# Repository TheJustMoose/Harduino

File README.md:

# Harduino

HardDuino is a 'Hard Arduino'
This is the clone of Arduino.
Project goals:
* ease of fastening
* compatible shields
* small sizes

How to use?

Copy content of template dir into C:\Program Files\KiCad\share\kicad\template\HardDuino

Add lib folder into KiCad libraries

Create 'new project from template' Harduino

Create your shield!
(Or use existing shield)

Enjoy!

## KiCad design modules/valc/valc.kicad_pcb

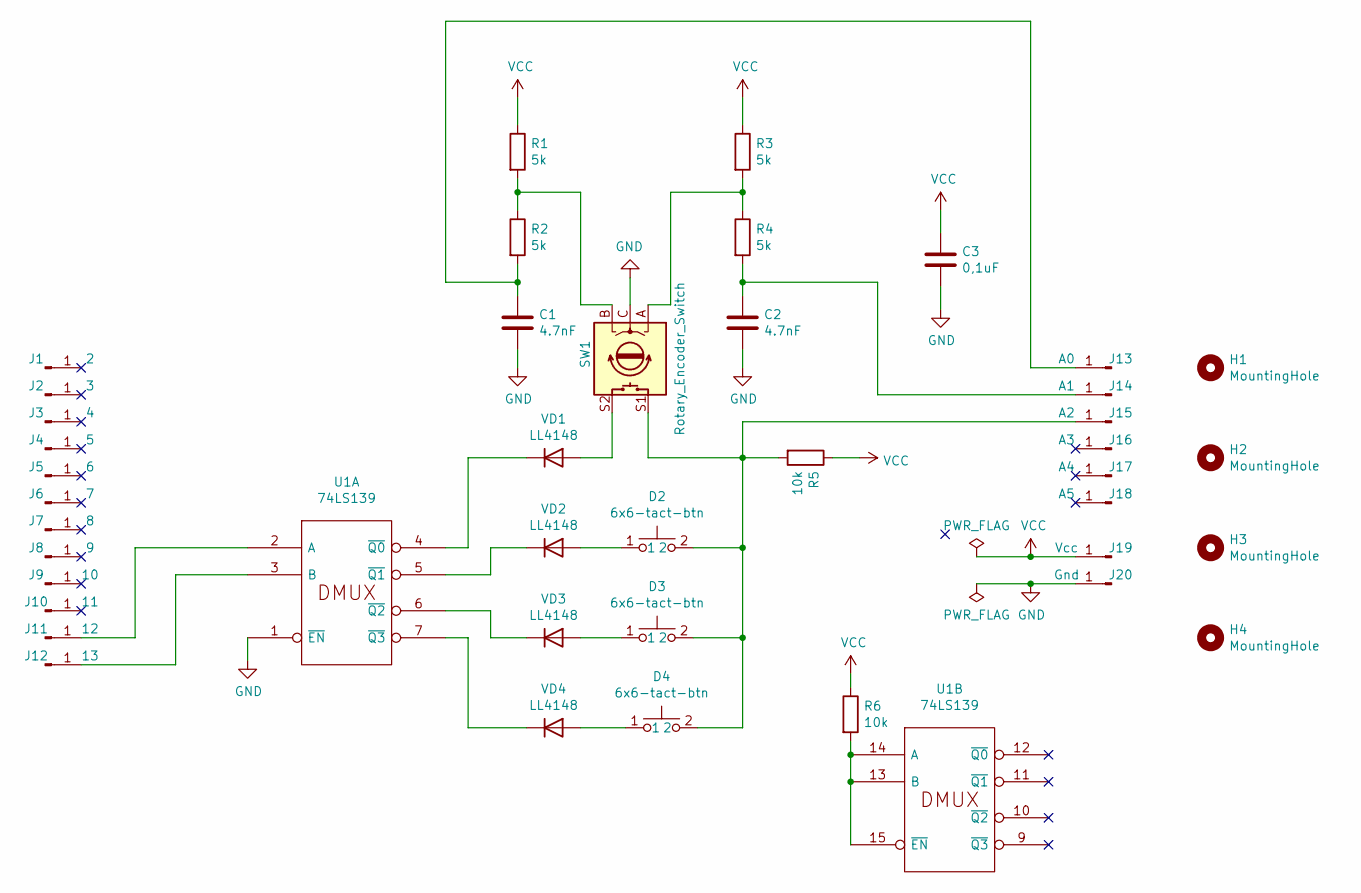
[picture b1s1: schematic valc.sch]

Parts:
C1, C2: 4.7nF; C_0805_2012Metric_Pad1.15x1.40mm_HandSolder
C3: 0,1uF; C_0805_2012Metric_Pad1.15x1.40mm_HandSolder
D2, D3, D4: 6x6-tact-btn
H1, H2, H3, H4: MountingHole; MountingHole_3.2mm_M3
J1: 2; PinHeader_1x01_P2.54mm_Vertical
J2: 3; PinHeader_1x01_P2.54mm_Vertical
J3: 4; PinHeader_1x01_P2.54mm_Vertical
J4: 5; PinHeader_1x01_P2.54mm_Vertical
J5: 6; PinHeader_1x01_P2.54mm_Vertical
J6: 7; PinHeader_1x01_P2.54mm_Vertical
J7: 8; PinHeader_1x01_P2.54mm_Vertical
J8: 9; PinHeader_1x01_P2.54mm_Vertical
J9: 10; PinHeader_1x01_P2.54mm_Vertical
J10: 11; PinHeader_1x01_P2.54mm_Vertical
J11: 12; PinHeader_1x01_P2.54mm_Vertical
J12: 13; PinHeader_1x01_P2.54mm_Vertical
J13: A0; PinHeader_1x01_P2.54mm_Vertical
J14: A1; PinHeader_1x01_P2.54mm_Vertical
J15: A2; PinHeader_1x01_P2.54mm_Vertical
J16: A3; PinHeader_1x01_P2.54mm_Vertical
J17: A4; PinHeader_1x01_P2.54mm_Vertical
J18: A5; PinHeader_1x01_P2.54mm_Vertical
J19: Vcc; PinHeader_1x01_P2.54mm_Vertical
J20: Gnd; PinHeader_1x01_P2.54mm_Vertical
R1, R2, R3, R4: 5k; R_0805_2012Metric_Pad1.15x1.40mm_HandSolder
R5, R6: 10k; R_0805_2012Metric_Pad1.15x1.40mm_HandSolder
SW1: Rotary_Encoder_Switch; RotaryEncoder_Alps_EC11E-Switch_Vertical_H20mm
U1: 74LS139; SOIC-16_3.9x9.9mm_P1.27mm
VD1, VD2, VD3, VD4: LL4148; D_MiniMELF

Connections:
GND: C1.2, C2.2, C3.2, J20.1, SW1.C, U1.1 (~EN), U1.8 (GND)
unnamed: C1.1, J13.1, R2.2
unnamed: C2.1, J14.1, R4.2
unnamed: D2.1, VD2.2 (A)
unnamed: D2.2, D3.2, D4.2, J15.1, R5.2, SW1.S1
unnamed: D3.1, VD3.2 (A)
unnamed: D4.1, VD4.2 (A)
unnamed: J11.1, U1.2 (A)
unnamed: J12.1, U1.3 (B)
unnamed: R1.2, R2.1, SW1.B
unnamed: R3.2, R4.1, SW1.A
unnamed: R6.2, U1.13 (B), U1.14 (A), U1.15 (~EN)
unnamed: SW1.S2, VD1.2 (A)
unnamed: U1.4 (~Q0), VD1.1 (K)
unnamed: U1.5 (~Q1), VD2.1 (K)
unnamed: U1.6 (~Q2), VD3.1 (K)
unnamed: U1.7 (~Q3), VD4.1 (K)
VCC: C3.1, J19.1, R1.1, R3.1, R5.1, R6.1, U1.16 (VCC)

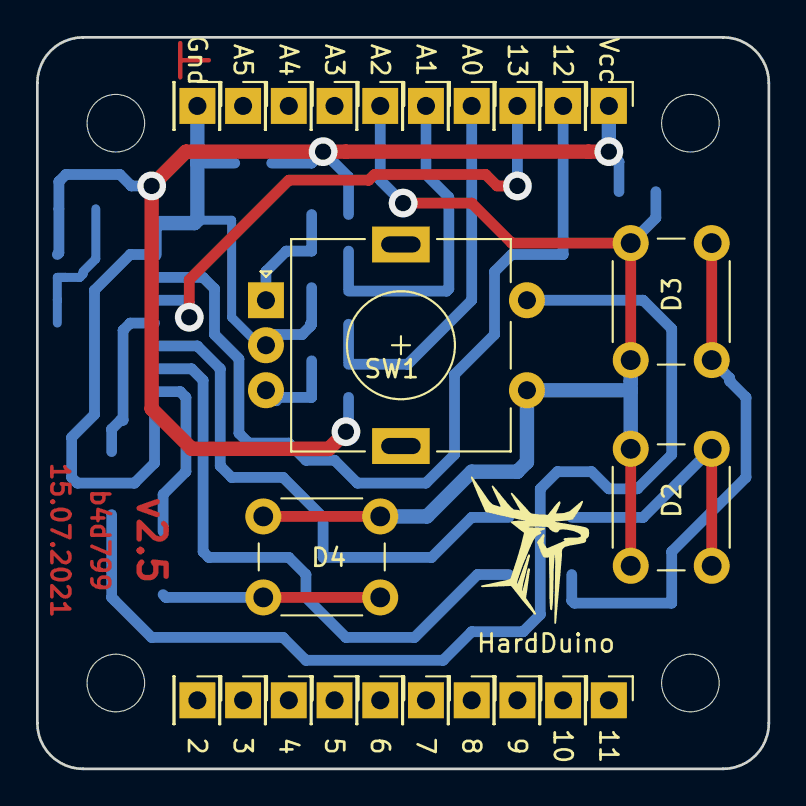
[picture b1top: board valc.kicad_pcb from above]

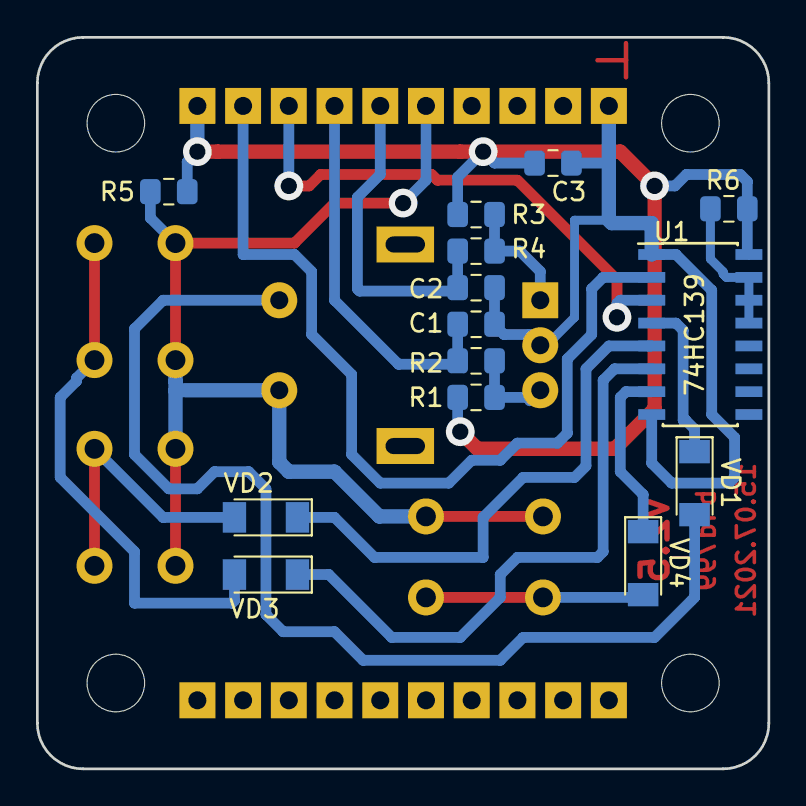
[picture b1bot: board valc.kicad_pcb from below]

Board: 2 copper layers, 40.6 x 40.6 mm, 42 parts (14 on the bottom side), 18 nets.

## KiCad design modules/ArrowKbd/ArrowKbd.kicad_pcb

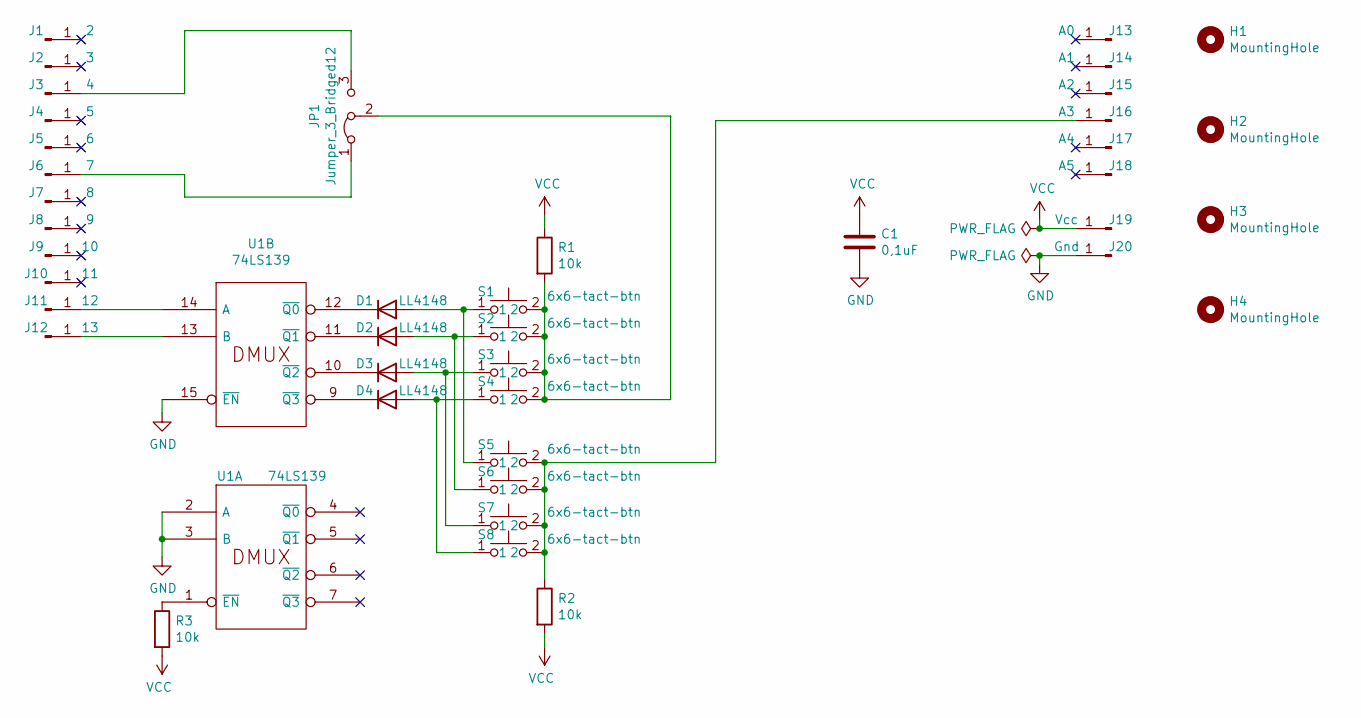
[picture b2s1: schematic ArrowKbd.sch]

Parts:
C1: 0,1uF; C_0805_2012Metric_Pad1.15x1.40mm_HandSolder
D1, D2, D3, D4: LL4148; D_MiniMELF
H1, H2, H3, H4: MountingHole; MountingHole_3.2mm_M3
J1: 2; PinHeader_1x01_P2.54mm_Vertical
J2: 3; PinHeader_1x01_P2.54mm_Vertical
J3: 4; PinHeader_1x01_P2.54mm_Vertical
J4: 5; PinHeader_1x01_P2.54mm_Vertical
J5: 6; PinHeader_1x01_P2.54mm_Vertical
J6: 7; PinHeader_1x01_P2.54mm_Vertical
J7: 8; PinHeader_1x01_P2.54mm_Vertical
J8: 9; PinHeader_1x01_P2.54mm_Vertical
J9: 10; PinHeader_1x01_P2.54mm_Vertical
J10: 11; PinHeader_1x01_P2.54mm_Vertical
J11: 12; PinHeader_1x01_P2.54mm_Vertical
J12: 13; PinHeader_1x01_P2.54mm_Vertical
J13: A0; PinHeader_1x01_P2.54mm_Vertical
J14: A1; PinHeader_1x01_P2.54mm_Vertical
J15: A2; PinHeader_1x01_P2.54mm_Vertical
J16: A3; PinHeader_1x01_P2.54mm_Vertical
J17: A4; PinHeader_1x01_P2.54mm_Vertical
J18: A5; PinHeader_1x01_P2.54mm_Vertical
J19: Vcc; PinHeader_1x01_P2.54mm_Vertical
J20: Gnd; PinHeader_1x01_P2.54mm_Vertical
JP1: Jumper_3_Bridged12; PinHeader_1x03_P2.54mm_Vertical
R1, R2, R3: 10k; R_0805_2012Metric_Pad1.15x1.40mm_HandSolder
S1, S2, S3, S4, S5, S6, S7, S8: 6x6-tact-btn
U1: 74LS139; SOIC-16_3.9x9.9mm_P1.27mm

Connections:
GND: C1.2, J20.1, U1.2 (A), U1.3 (B), U1.8 (GND), U1.15 (~EN)
unnamed: D1.1 (K), U1.12 (~Q0)
unnamed: D1.2 (A), S1.1, S5.1
unnamed: D2.1 (K), U1.11 (~Q1)
unnamed: D2.2 (A), S2.1, S6.1
unnamed: D3.1 (K), U1.10 (~Q2)
unnamed: D3.2 (A), S3.1, S7.1
unnamed: D4.1 (K), U1.9 (~Q3)
unnamed: D4.2 (A), S4.1, S8.1
unnamed: J3.1, JP1.3 (B)
unnamed: J6.1, JP1.1 (A)
unnamed: J11.1, U1.14 (A)
unnamed: J12.1, U1.13 (B)
unnamed: J16.1, R2.1, S5.2, S6.2, S7.2, S8.2
unnamed: JP1.2 (C), R1.2, S1.2, S2.2, S3.2, S4.2
unnamed: R3.1, U1.1 (~EN)
VCC: C1.1, J19.1, R1.1, R2.2, R3.2, U1.16 (VCC)

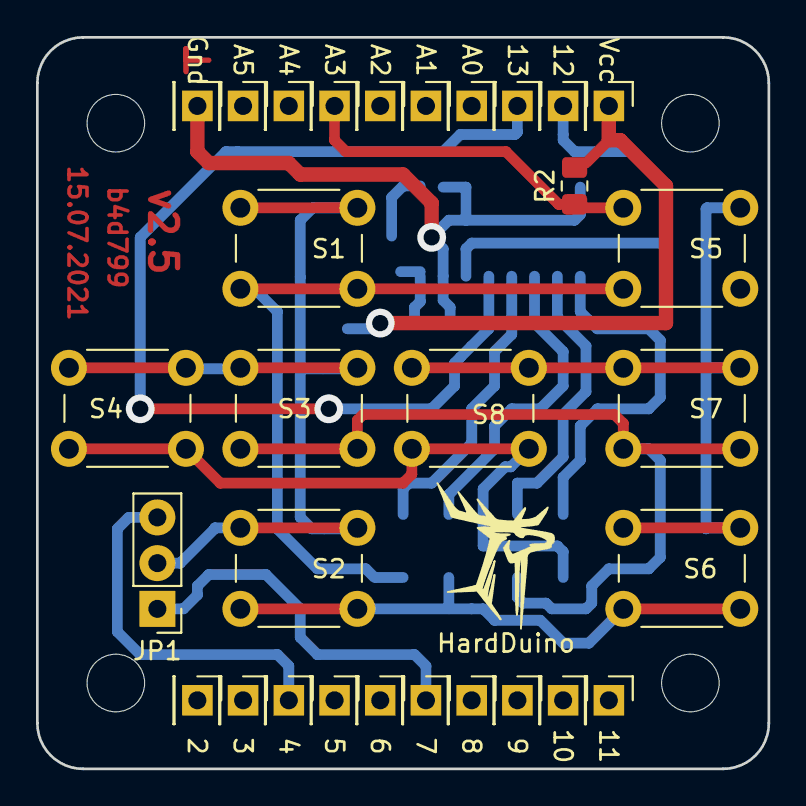
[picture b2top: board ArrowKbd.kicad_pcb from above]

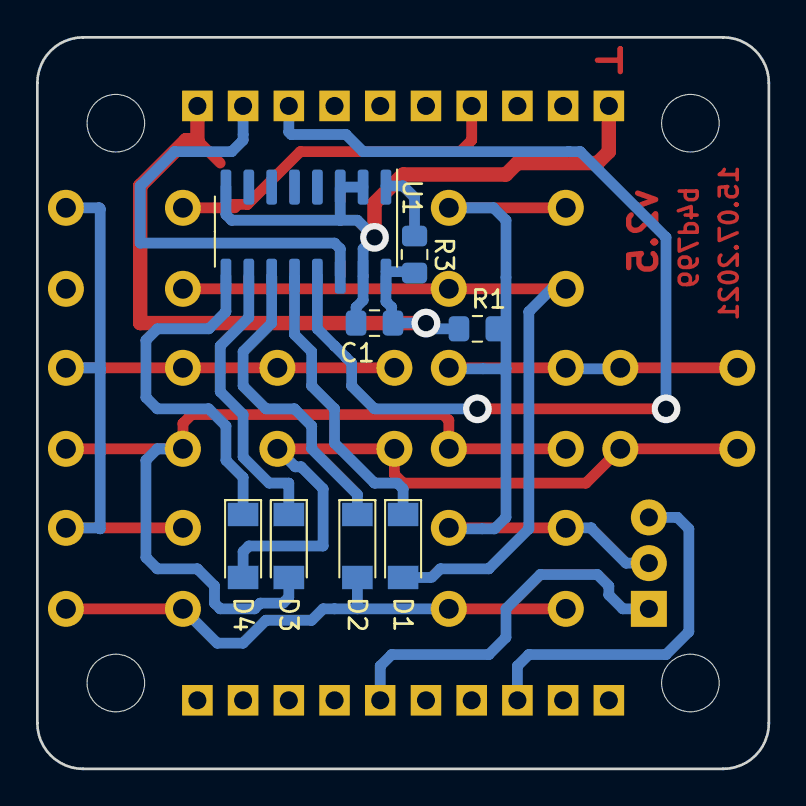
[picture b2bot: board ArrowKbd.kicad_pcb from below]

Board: 2 copper layers, 40.6 x 40.6 mm, 42 parts (8 on the bottom side), 17 nets.

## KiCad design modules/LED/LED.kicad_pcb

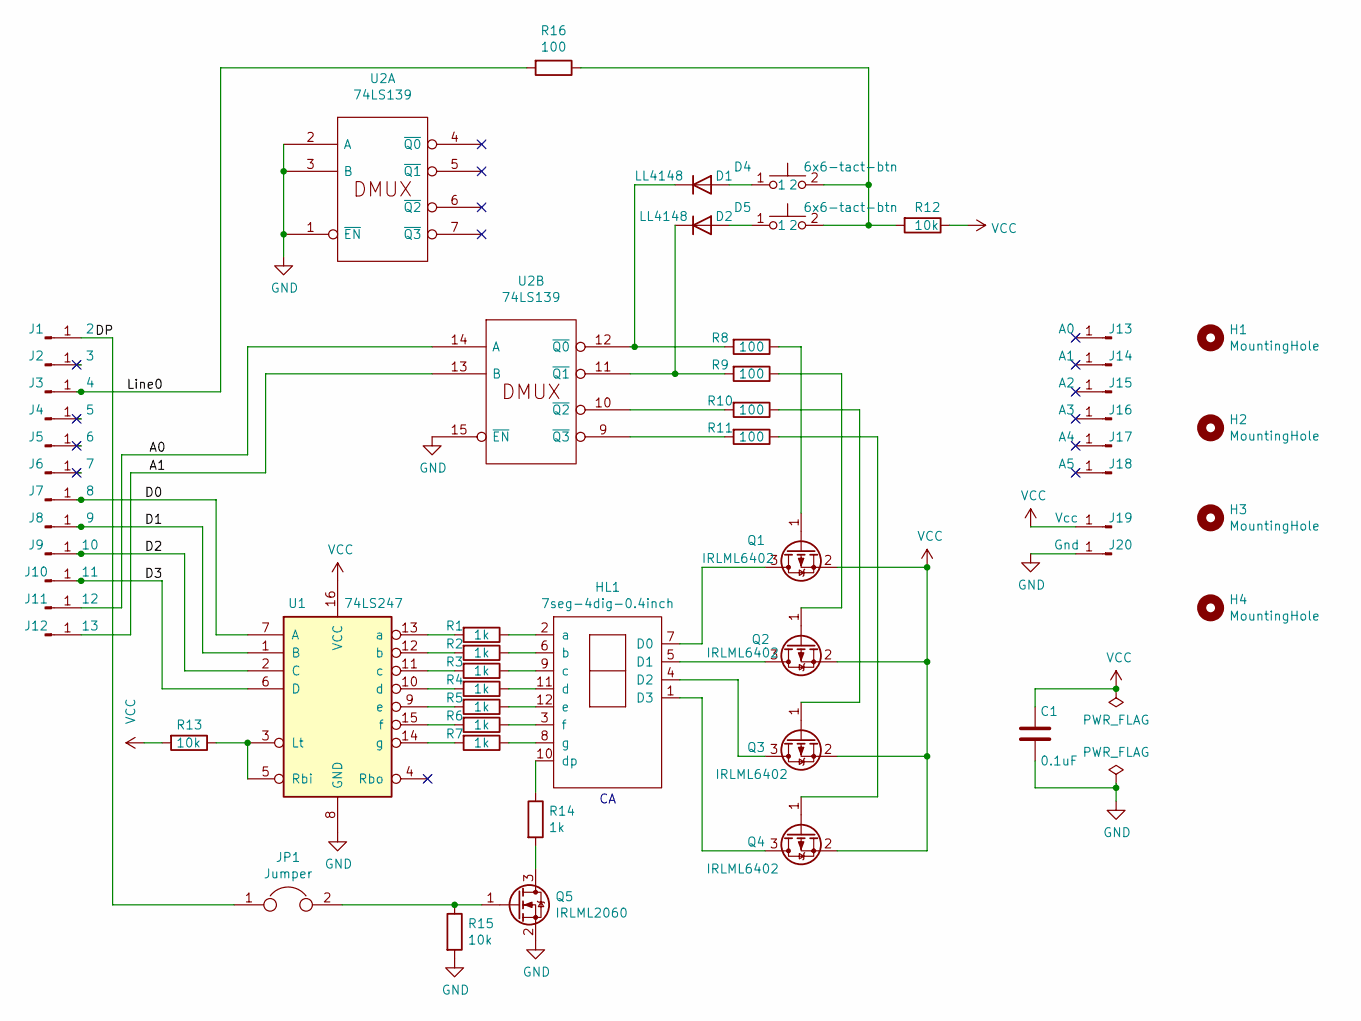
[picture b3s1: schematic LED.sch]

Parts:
C1: 0.1uF; C_0805_2012Metric_Pad1.15x1.40mm_HandSolder
D1, D2: LL4148; D_MiniMELF
D4, D5: 6x6-tact-btn
H1, H2, H3, H4: MountingHole; MountingHole_3.2mm_M3
HL1: 7seg-4dig-0.4inch
J1: 2; PinHeader_1x01_P2.54mm_Vertical
J2: 3; PinHeader_1x01_P2.54mm_Vertical
J3: 4; PinHeader_1x01_P2.54mm_Vertical
J4: 5; PinHeader_1x01_P2.54mm_Vertical
J5: 6; PinHeader_1x01_P2.54mm_Vertical
J6: 7; PinHeader_1x01_P2.54mm_Vertical
J7: 8; PinHeader_1x01_P2.54mm_Vertical
J8: 9; PinHeader_1x01_P2.54mm_Vertical
J9: 10; PinHeader_1x01_P2.54mm_Vertical
J10: 11; PinHeader_1x01_P2.54mm_Vertical
J11: 12; PinHeader_1x01_P2.54mm_Vertical
J12: 13; PinHeader_1x01_P2.54mm_Vertical
J13: A0; PinHeader_1x01_P2.54mm_Vertical
J14: A1; PinHeader_1x01_P2.54mm_Vertical
J15: A2; PinHeader_1x01_P2.54mm_Vertical
J16: A3; PinHeader_1x01_P2.54mm_Vertical
J17: A4; PinHeader_1x01_P2.54mm_Vertical
J18: A5; PinHeader_1x01_P2.54mm_Vertical
J19: Vcc; PinHeader_1x01_P2.54mm_Vertical
J20: Gnd; PinHeader_1x01_P2.54mm_Vertical
JP1: Jumper; PinHeader_1x02_P2.54mm_Vertical
Q1, Q2, Q3, Q4: IRLML6402; SOT-23
Q5: IRLML2060; SOT-23
R1, R2, R3, R4, R5, R6, R7, R14: 1k; R_0805_2012Metric_Pad1.15x1.40mm_HandSolder
R8, R9, R10, R11, R16: 100; R_0805_2012Metric_Pad1.15x1.40mm_HandSolder
R12, R13, R15: 10k; R_0805_2012Metric_Pad1.15x1.40mm_HandSolder
U1: 74LS247; SOIC-16_3.9x9.9mm_P1.27mm
U2: 74LS139; SOIC-16_3.9x9.9mm_P1.27mm

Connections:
/A0: J11.1, U2.14 (A)
/A1: J12.1, U2.13 (B)
/D0: J7.1, U1.7 (A)
/D1: J8.1, U1.1 (B)
/D2: J9.1, U1.2 (C)
/D3: J10.1, U1.6 (D)
/DP: J1.1, JP1.1
/Line0: J3.1, R16.2
GND: C1.2, J20.1, Q5.2 (S), R15.2, U1.8 (GND), U2.1 (~EN), U2.2 (A), U2.3 (B), U2.8 (GND), U2.15 (~EN)
unnamed: D1.1 (K), R8.2, U2.12 (~Q0)
unnamed: D1.2 (A), D4.1
unnamed: D2.1 (K), R9.2, U2.11 (~Q1)
unnamed: D2.2 (A), D5.1
unnamed: D4.2, D5.2, R12.2, R16.1
unnamed: HL1.1 (D3), Q4.3 (D)
unnamed: HL1.2 (a), R1.1
unnamed: HL1.3 (f), R6.1
unnamed: HL1.4 (D2), Q3.3 (D)
unnamed: HL1.5 (D1), Q2.3 (D)
unnamed: HL1.6 (b), R2.1
unnamed: HL1.7 (D0), Q1.3 (D)
unnamed: HL1.8 (g), R7.1
unnamed: HL1.9 (c), R3.1
unnamed: HL1.10 (dp), R14.1
unnamed: HL1.11 (d), R4.1
unnamed: HL1.12 (e), R5.1
unnamed: JP1.2, Q5.1 (G), R15.1
unnamed: Q1.1 (G), R8.1
unnamed: Q2.1 (G), R9.1
unnamed: Q3.1 (G), R10.1
unnamed: Q4.1 (G), R11.1
unnamed: Q5.3 (D), R14.2
unnamed: R1.2, U1.13 (a)
unnamed: R2.2, U1.12 (b)
unnamed: R3.2, U1.11 (c)
unnamed: R4.2, U1.10 (d)
unnamed: R5.2, U1.9 (e)
unnamed: R6.2, U1.15 (f)
unnamed: R7.2, U1.14 (g)
unnamed: R10.2, U2.10 (~Q2)
unnamed: R11.2, U2.9 (~Q3)
unnamed: R13.1, U1.3 (Lt), U1.5 (Rbi)
VCC: C1.1, J19.1, Q1.2 (S), Q2.2 (S), Q3.2 (S), Q4.2 (S), R12.1, R13.2, U1.16 (VCC), U2.16 (VCC)

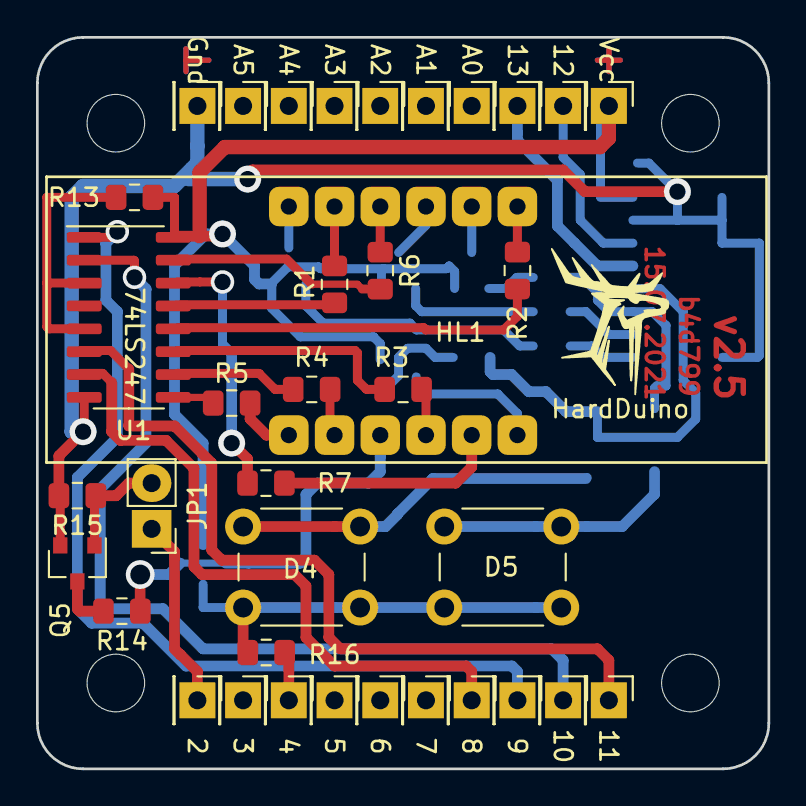
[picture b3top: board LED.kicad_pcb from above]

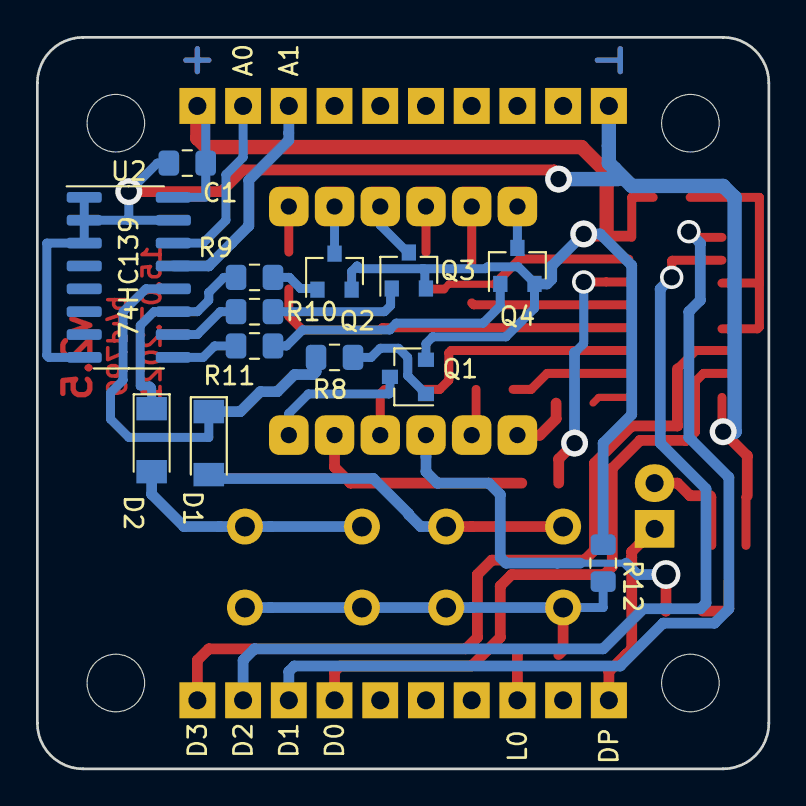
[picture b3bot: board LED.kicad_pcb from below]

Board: 2 copper layers, 40.6 x 40.6 mm, 54 parts (13 on the bottom side), 43 nets.

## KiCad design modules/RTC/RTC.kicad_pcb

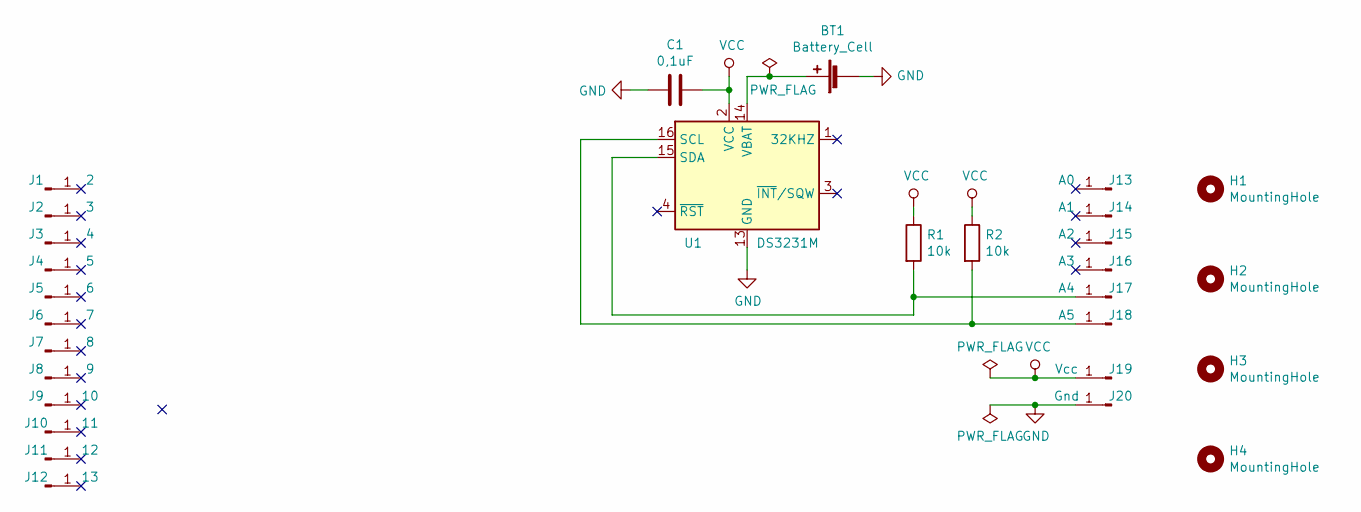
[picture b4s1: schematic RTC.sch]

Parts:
BT1: Battery_Cell; CR1220-holder
C1: 0,1uF; C_0805_2012Metric_Pad1.15x1.40mm_HandSolder
H1, H2, H3, H4: MountingHole; MountingHole_3.2mm_M3
J1: 2; PinHeader_1x01_P2.54mm_Vertical
J2: 3; PinHeader_1x01_P2.54mm_Vertical
J3: 4; PinHeader_1x01_P2.54mm_Vertical
J4: 5; PinHeader_1x01_P2.54mm_Vertical
J5: 6; PinHeader_1x01_P2.54mm_Vertical
J6: 7; PinHeader_1x01_P2.54mm_Vertical
J7: 8; PinHeader_1x01_P2.54mm_Vertical
J8: 9; PinHeader_1x01_P2.54mm_Vertical
J9: 10; PinHeader_1x01_P2.54mm_Vertical
J10: 11; PinHeader_1x01_P2.54mm_Vertical
J11: 12; PinHeader_1x01_P2.54mm_Vertical
J12: 13; PinHeader_1x01_P2.54mm_Vertical
J13: A0; PinHeader_1x01_P2.54mm_Vertical
J14: A1; PinHeader_1x01_P2.54mm_Vertical
J15: A2; PinHeader_1x01_P2.54mm_Vertical
J16: A3; PinHeader_1x01_P2.54mm_Vertical
J17: A4; PinHeader_1x01_P2.54mm_Vertical
J18: A5; PinHeader_1x01_P2.54mm_Vertical
J19: Vcc; PinHeader_1x01_P2.54mm_Vertical
J20: Gnd; PinHeader_1x01_P2.54mm_Vertical
R1, R2: 10k; R_0805_2012Metric_Pad1.15x1.40mm_HandSolder
U1: DS3231M; SOIC-16W_7.5x10.3mm_P1.27mm

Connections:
GND: BT1.2 (-), C1.2, J20.1, U1.5 (GND), U1.6 (GND), U1.7 (GND), U1.8 (GND), U1.9 (GND), U1.10 (GND), U1.11 (GND), U1.12 (GND), U1.13 (GND)
unnamed: BT1.1 (+), U1.14 (VBAT)
unnamed: J17.1, R1.2, U1.15 (SDA)
unnamed: J18.1, R2.2, U1.16 (SCL)
VCC: C1.1, J19.1, R1.1, R2.1, U1.2 (VCC)

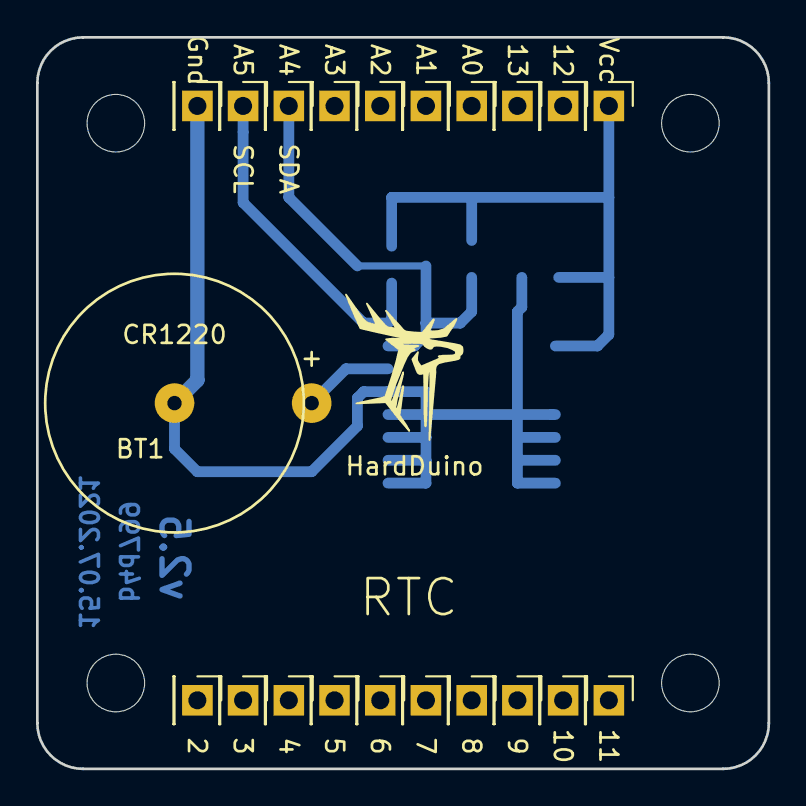
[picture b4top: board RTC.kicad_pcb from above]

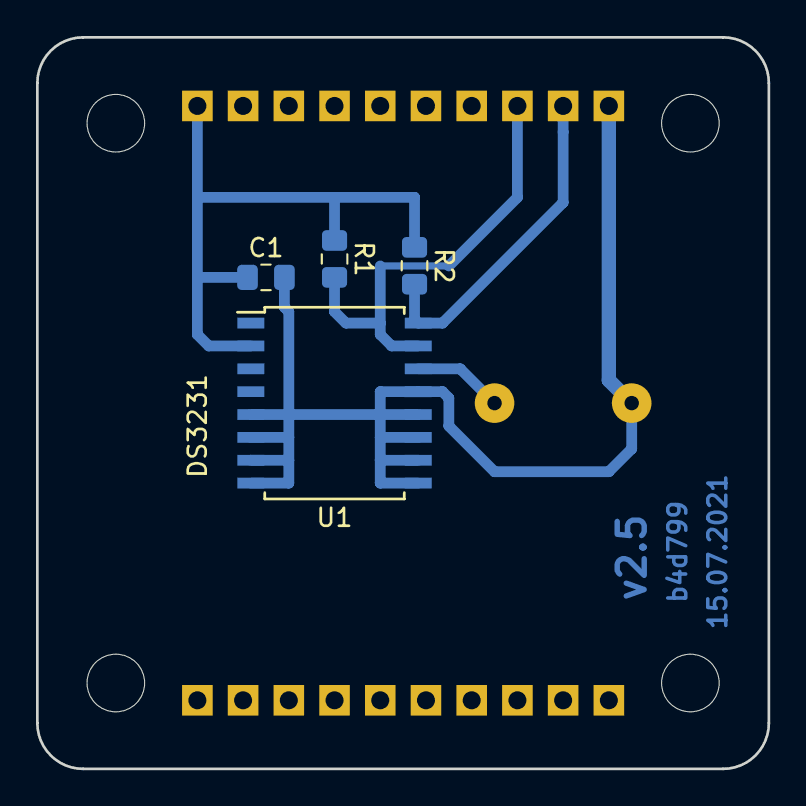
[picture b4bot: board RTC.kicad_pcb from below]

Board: 2 copper layers, 40.6 x 40.6 mm, 29 parts (4 on the bottom side), 5 nets.

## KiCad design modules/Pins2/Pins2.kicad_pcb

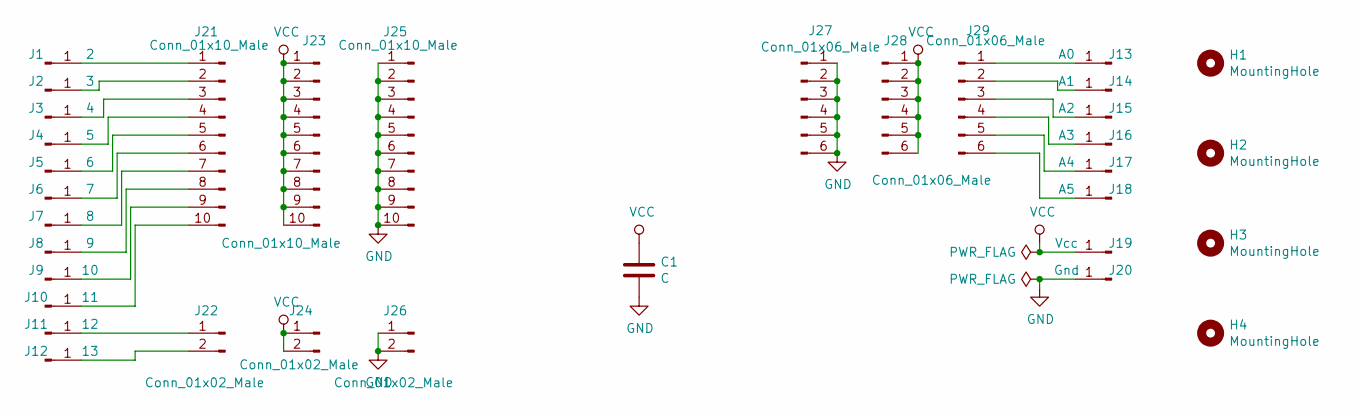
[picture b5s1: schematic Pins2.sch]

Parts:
C1: C; C_Disc_D4.7mm_W2.5mm_P5.00mm
H1, H2, H3, H4: MountingHole; MountingHole_3.2mm_M3
J1: 2; PinHeader_1x01_P2.54mm_Vertical
J2: 3; PinHeader_1x01_P2.54mm_Vertical
J3: 4; PinHeader_1x01_P2.54mm_Vertical
J4: 5; PinHeader_1x01_P2.54mm_Vertical
J5: 6; PinHeader_1x01_P2.54mm_Vertical
J6: 7; PinHeader_1x01_P2.54mm_Vertical
J7: 8; PinHeader_1x01_P2.54mm_Vertical
J8: 9; PinHeader_1x01_P2.54mm_Vertical
J9: 10; PinHeader_1x01_P2.54mm_Vertical
J10: 11; PinHeader_1x01_P2.54mm_Vertical
J11: 12; PinHeader_1x01_P2.54mm_Vertical
J12: 13; PinHeader_1x01_P2.54mm_Vertical
J13: A0; PinHeader_1x01_P2.54mm_Vertical
J14: A1; PinHeader_1x01_P2.54mm_Vertical
J15: A2; PinHeader_1x01_P2.54mm_Vertical
J16: A3; PinHeader_1x01_P2.54mm_Vertical
J17: A4; PinHeader_1x01_P2.54mm_Vertical
J18: A5; PinHeader_1x01_P2.54mm_Vertical
J19: Vcc; PinHeader_1x01_P2.54mm_Vertical
J20: Gnd; PinHeader_1x01_P2.54mm_Vertical
J21, J23: Conn_01x10_Male; PinHeader_1x10_P2.54mm_Vertical
J22, J24: Conn_01x02_Male; PinHeader_1x02_P2.54mm_Vertical
J25: Conn_01x10_Male; PinHeader_1x10_P2.54mm_Horizontal
J26: Conn_01x02_Male; PinHeader_1x02_P2.54mm_Horizontal
J27: Conn_01x06_Male; PinHeader_1x06_P2.54mm_Horizontal
J28, J29: Conn_01x06_Male; PinHeader_1x06_P2.54mm_Vertical

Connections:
GND: C1.2, J20.1, J25.1, J25.2, J25.3, J25.4, J25.5, J25.6, J25.7, J25.8, J25.9, J25.10, J26.1, J26.2, J27.1, J27.2, J27.3, J27.4, J27.5, J27.6
unnamed: J1.1, J21.1
unnamed: J2.1, J21.2
unnamed: J10.1, J21.10
unnamed: J11.1, J22.1
unnamed: J12.1, J22.2
unnamed: J13.1, J29.1
unnamed: J14.1, J29.2
unnamed: J15.1, J29.3
unnamed: J16.1, J29.4
unnamed: J17.1, J29.5
unnamed: J18.1, J29.6
unnamed: J3.1, J21.3
unnamed: J4.1, J21.4
unnamed: J5.1, J21.5
unnamed: J6.1, J21.6
unnamed: J7.1, J21.7
unnamed: J8.1, J21.8
unnamed: J9.1, J21.9
VCC: C1.1, J19.1, J23.1, J23.2, J23.3, J23.4, J23.5, J23.6, J23.7, J23.8, J23.9, J23.10, J24.1, J24.2, J28.1, J28.2, J28.3, J28.4, J28.5, J28.6

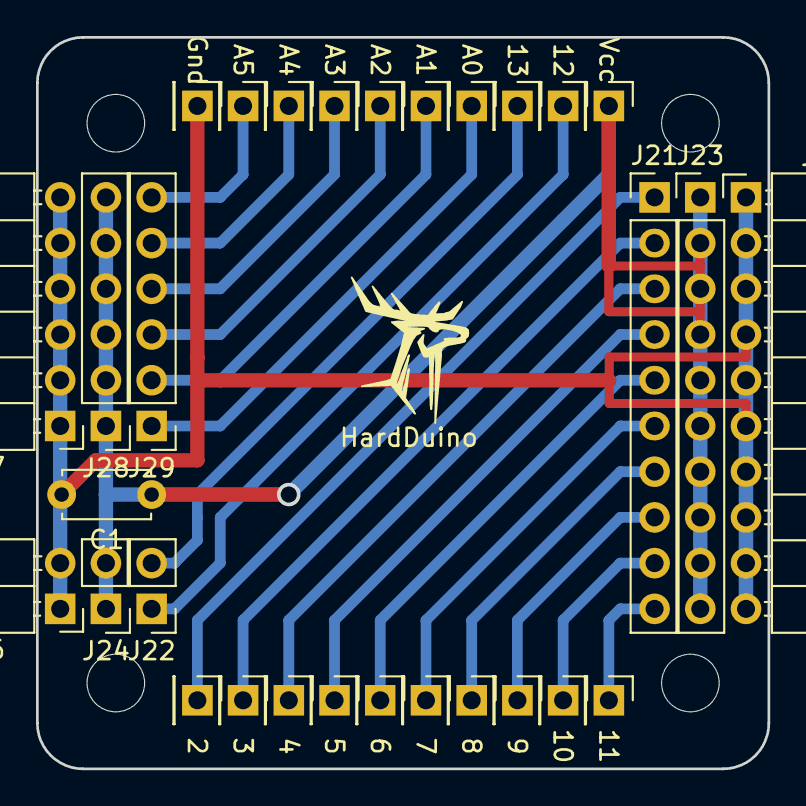
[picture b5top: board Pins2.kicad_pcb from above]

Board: 2 copper layers, 40.6 x 40.6 mm, 34 parts (0 on the bottom side), 20 nets.

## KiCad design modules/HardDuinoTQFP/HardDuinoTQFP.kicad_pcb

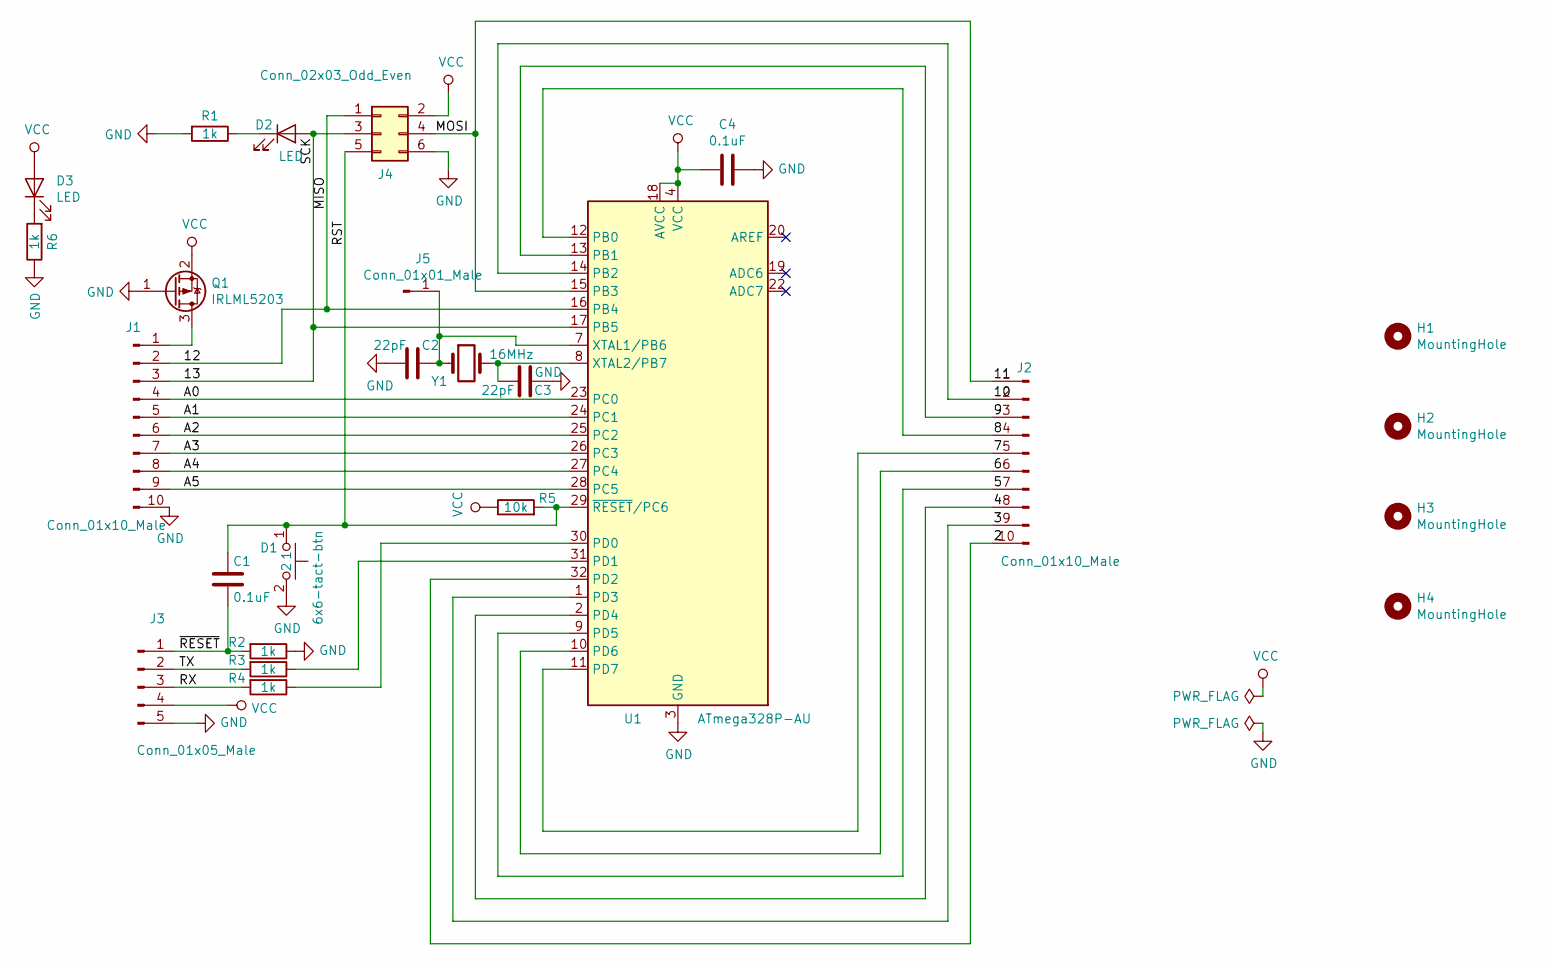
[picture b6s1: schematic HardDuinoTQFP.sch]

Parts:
C1, C4: 0.1uF; C_0805_2012Metric_Pad1.15x1.40mm_HandSolder
C2, C3: 22pF; C_0805_2012Metric_Pad1.15x1.40mm_HandSolder
D1: 6x6-tact-btn
D2, D3: LED; LED_0805_2012Metric_Pad1.15x1.40mm_HandSolder
H1, H2, H3, H4: MountingHole; MountingHole_3.2mm_M3
J1, J2: Conn_01x10_Male; PinSocket_1x10_P2.54mm_Vertical
J3: Conn_01x05_Male; PinHeader_1x05_P2.54mm_Vertical
J4: Conn_02x03_Odd_Even; PinHeader_2x03_P2.54mm_Vertical
J5: Conn_01x01_Male; PinHeader_1x01_P2.54mm_Vertical
Q1: IRLML5203; SOT-23
R1, R2, R3, R4, R6: 1k; R_0805_2012Metric_Pad1.15x1.40mm_HandSolder
R5: 10k; R_0805_2012Metric_Pad1.15x1.40mm_HandSolder
U1: ATmega328P-AU; TQFP-32_7x7mm_P0.8mm
Y1: 16MHz; Crystal_HC49-U_Vertical

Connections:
/2: J2.10, U1.32 (PD2)
/3: J2.9, U1.1 (PD3)
/4: J2.8, U1.2 (PD4)
/5: J2.7, U1.9 (PD5)
/6: J2.6, U1.10 (PD6)
/7: J2.5, U1.11 (PD7)
/8: J2.4, U1.12 (PB0)
/9: J2.3, U1.13 (PB1)
/10: J2.2, U1.14 (PB2)
/11: J2.1, J4.4, U1.15 (PB3)
/12: J1.2, J4.1, U1.16 (PB4)
/13: D2.2 (A), J1.3, J4.3, U1.17 (PB5)
/A0: J1.4, U1.23 (PC0)
/A1: J1.5, U1.24 (PC1)
/A2: J1.6, U1.25 (PC2)
/A3: J1.7, U1.26 (PC3)
/A4: J1.8, U1.27 (PC4)
/A5: J1.9, U1.28 (PC5)
/RST: C1.1, D1.1, J4.5, R5.2, U1.29 (~RESET~/PC6)
/RX: J3.3, R4.2
/TX: J3.2, R3.2
/~RESET: C1.2, J3.1, R2.2
GND: C2.2, C3.1, C4.1, D1.2, J1.10, J3.5, J4.6, Q1.1 (G), R1.2, R2.1, R6.1, U1.3 (GND), U1.5 (GND), U1.21 (GND)
unnamed 23: C2.1, J5.1, U1.7 (XTAL1/PB6), Y1.1; also elsewhere on the board
unnamed 24: C3.2, U1.8 (XTAL2/PB7), Y1.2; also elsewhere on the board
unnamed: D2.1 (K), R1.1
unnamed: D3.1 (K), R6.2
unnamed: J1.1, Q1.3 (D)
unnamed: R3.1, U1.31 (PD1)
unnamed: R4.1, U1.30 (PD0)
unnamed 30: U1.20 (AREF); also elsewhere on the board
VCC: C4.2, D3.2 (A), J3.4, J4.2, Q1.2 (S), R5.1, U1.4 (VCC), U1.6 (VCC), U1.18 (AVCC); also elsewhere on the board

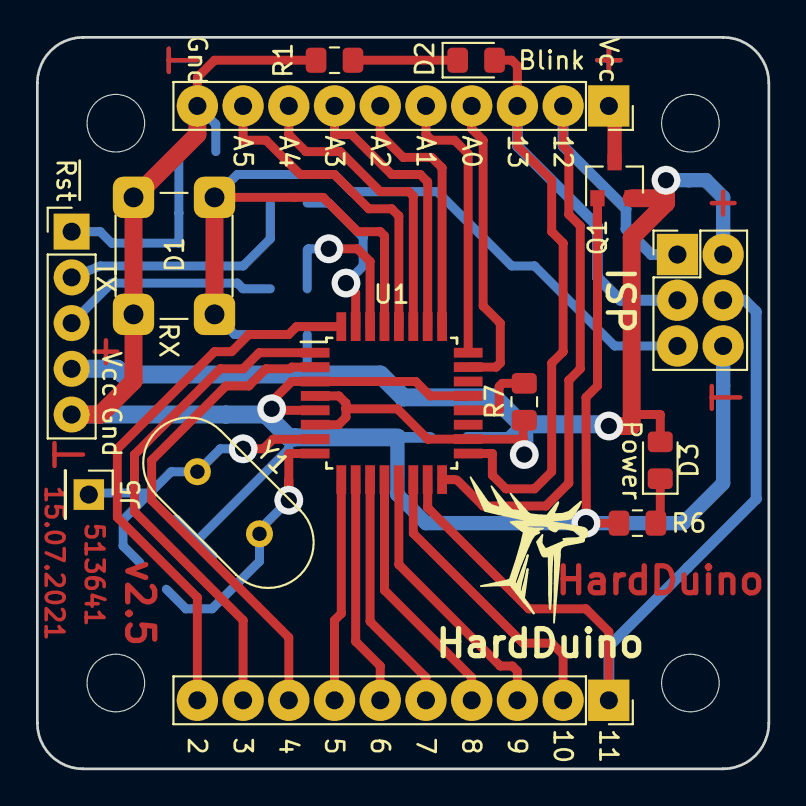
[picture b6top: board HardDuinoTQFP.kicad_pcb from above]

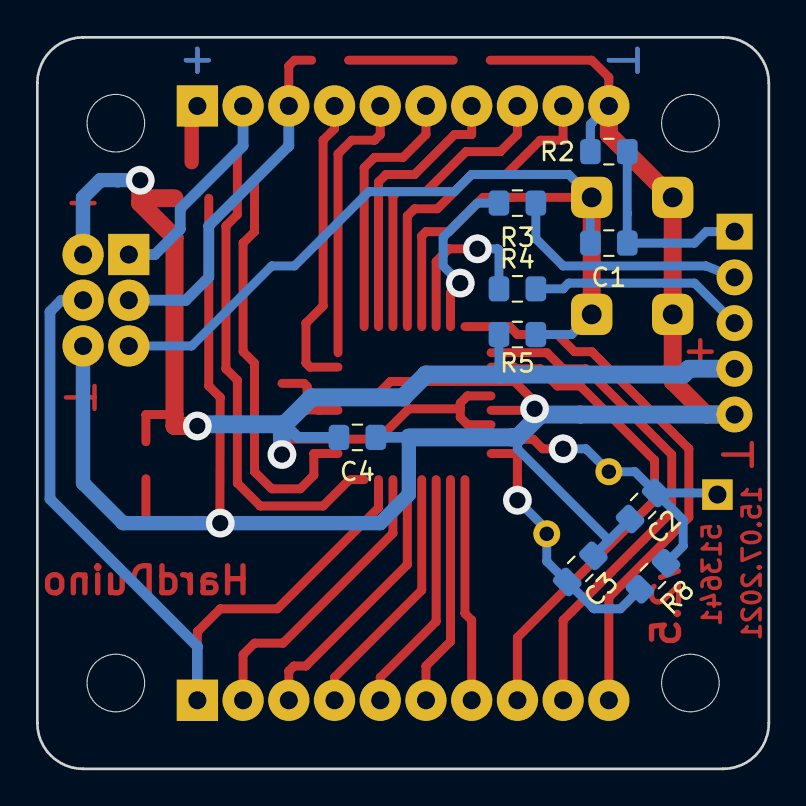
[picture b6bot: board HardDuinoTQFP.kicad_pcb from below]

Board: 2 copper layers, 40.6 x 40.6 mm, 27 parts (9 on the bottom side), 32 nets.

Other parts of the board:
R7: 1k; R_0805_2012Metric_Pad1.15x1.40mm_HandSolder
R8: 1M; R_0805_2012Metric_Pad1.15x1.40mm_HandSolder

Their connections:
unnamed 23: R8.1; also elsewhere on the board
unnamed 24: R8.2; also elsewhere on the board
unnamed 30: R7.2; also elsewhere on the board
VCC: R7.1; also elsewhere on the board

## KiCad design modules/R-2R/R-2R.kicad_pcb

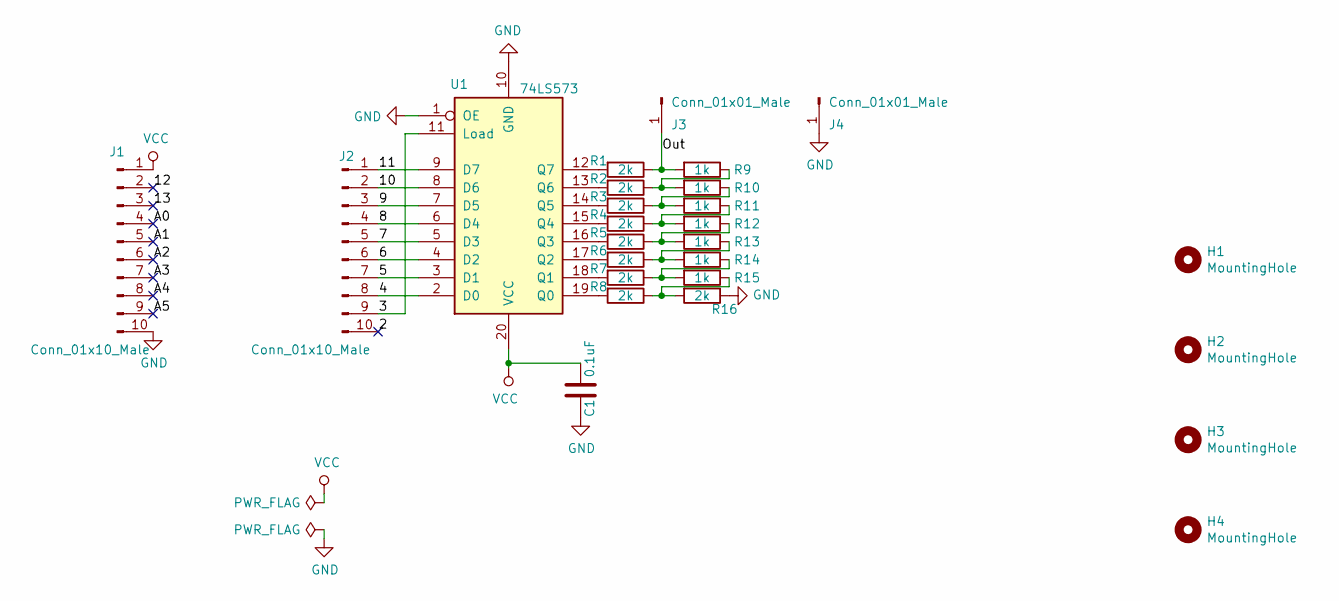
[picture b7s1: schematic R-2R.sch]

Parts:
C1: 0.1uF; C_0805_2012Metric_Pad1.15x1.40mm_HandSolder
H1, H2, H3, H4: MountingHole; MountingHole_3.2mm_M3
J1, J2: Conn_01x10_Male; PinSocket_1x10_P2.54mm_Vertical
J3, J4: Conn_01x01_Male; PinHeader_1x01_P2.54mm_Vertical
R1, R2, R3, R4, R5, R6, R7, R8, R16: 2k; R_0805_2012Metric_Pad1.15x1.40mm_HandSolder
R9, R10, R11, R12, R13, R14, R15: 1k; R_0805_2012Metric_Pad1.15x1.40mm_HandSolder
U1: 74LS573; SO-20_12.8x7.5mm_P1.27mm

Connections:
/2: J2.10
/3: J2.9, U1.11 (Load)
/4: J2.8, U1.2 (D0)
/5: J2.7, U1.3 (D1)
/6: J2.6, U1.4 (D2)
/7: J2.5, U1.5 (D3)
/8: J2.4, U1.6 (D4)
/9: J2.3, U1.7 (D5)
/10: J2.2, U1.8 (D6)
/11: J2.1, U1.9 (D7)
/12: J1.2
/13: J1.3
/A0: J1.4
/A1: J1.5
/A2: J1.6
/A3: J1.7
/A4: J1.8
/A5: J1.9
/Out: J3.1, R1.1, R9.2
GND: C1.1, J1.10, J4.1, R16.1, U1.1 (OE), U1.10 (GND)
unnamed: R1.2, U1.12 (Q7)
unnamed: R2.2, U1.13 (Q6)
unnamed: R3.2, U1.14 (Q5)
unnamed: R4.2, U1.15 (Q4)
unnamed: R5.2, U1.16 (Q3)
unnamed: R6.2, U1.17 (Q2)
unnamed: R7.2, U1.18 (Q1)
unnamed: R8.2, U1.19 (Q0)
unnamed: R3.1, R10.1, R11.2
unnamed: R2.1, R9.1, R10.2
unnamed: R4.1, R11.1, R12.2
unnamed: R5.1, R12.1, R13.2
unnamed: R6.1, R13.1, R14.2
unnamed: R7.1, R14.1, R15.2
unnamed: R8.1, R15.1, R16.2
VCC: C1.2, J1.1, U1.20 (VCC)
